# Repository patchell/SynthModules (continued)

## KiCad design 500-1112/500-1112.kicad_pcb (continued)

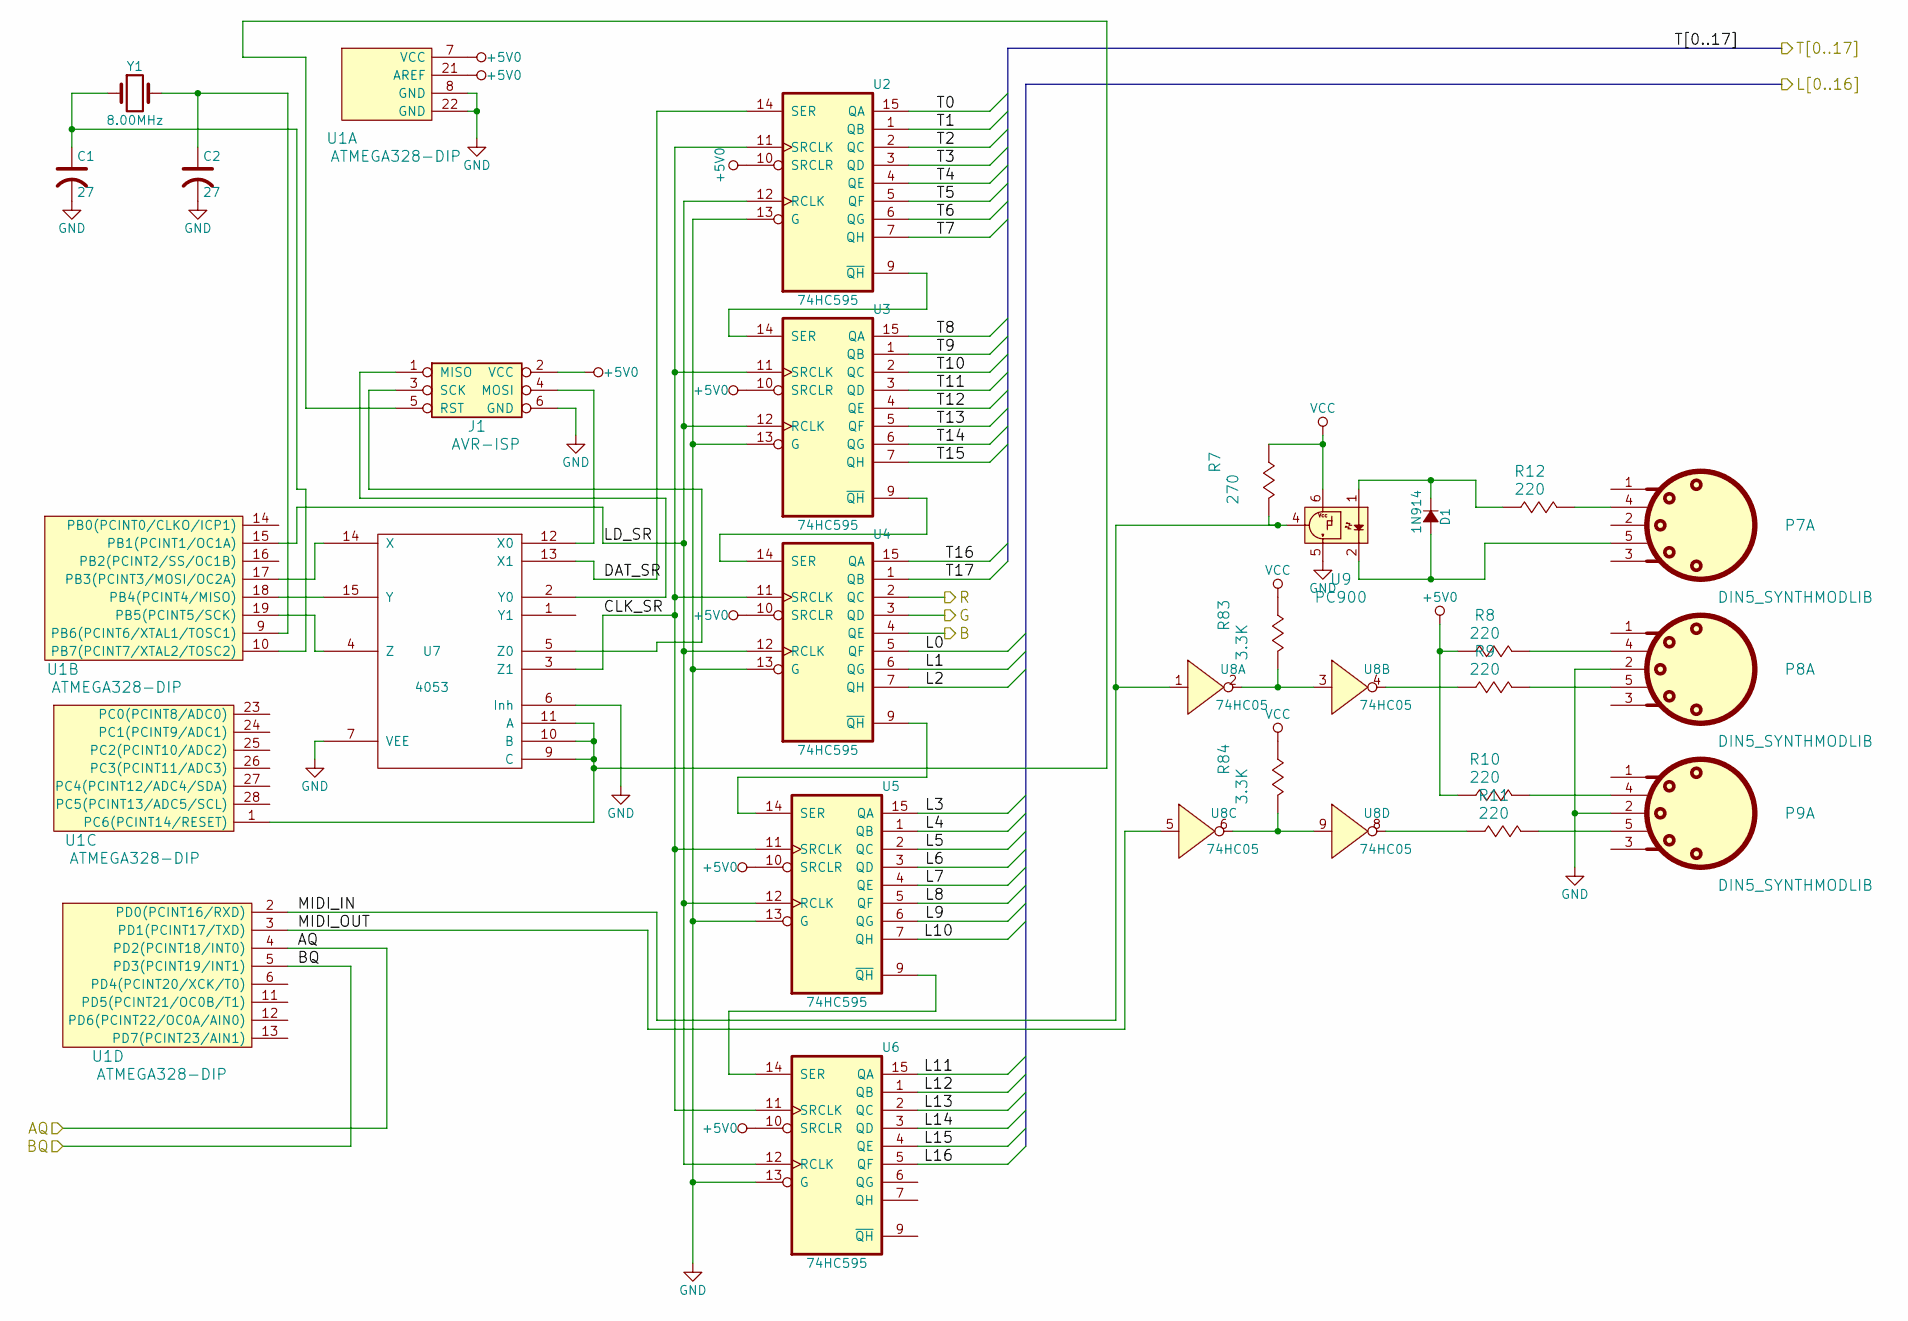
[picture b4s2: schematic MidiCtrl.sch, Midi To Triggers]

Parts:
C1, C2: 27; CAP-0.1
D1: 1N914; DIODE0.4
J1: AVR-ISP; IDC3X2
P7, P8, P9: DIN5_SYNTHMODLIB; DIN-5-PIN
R7: 270; AXIAL0.4
R8, R9, R10, R11, R12: 220; AXIAL0.4
R83, R84: 3.3K; AXIAL0.4
U1: ATMEGA328-DIP; DIP28.3
U2, U3, U4, U5, U6: 74HC595; DIP-20.3
U7: 4053; DIP16.3
U8: 74HC05; DIP-14.3
U9: PC900; DIP-6.3
Y1: 8.00MHz; XTAL

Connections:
+5V0: J1.2 (VCC), R8.1 (A), R10.1 (A), U1.7 (VCC), U1.21 (AREF), U2.10 (SRCLR), U3.10 (SRCLR), U4.10 (SRCLR), U5.10 (SRCLR), U6.10 (SRCLR); also elsewhere on the board
/Midi Controller/AQ: U1.4 (PD2(PCINT18/INT0)); also elsewhere on the board
/Midi Controller/B: U4.4 (QE); also elsewhere on the board
/Midi Controller/BQ: U1.5 (PD3(PCINT19/INT1)); also elsewhere on the board
/Midi Controller/CLK_SR: U2.11 (SRCLK), U3.11 (SRCLK), U4.11 (SRCLK), U5.11 (SRCLK), U6.11 (SRCLK), U7.3 (Z1)
/Midi Controller/DAT_SR: U2.14 (SER), U7.13 (X1)
/Midi Controller/G: U4.3 (QD); also elsewhere on the board
/Midi Controller/L0: U4.5 (QF); also elsewhere on the board
/Midi Controller/L1: U4.6 (QG); also elsewhere on the board
/Midi Controller/L2: U4.7 (QH); also elsewhere on the board
/Midi Controller/L3: U5.15 (QA); also elsewhere on the board
/Midi Controller/L4: U5.1 (QB); also elsewhere on the board
/Midi Controller/L5: U5.2 (QC); also elsewhere on the board
/Midi Controller/L6: U5.3 (QD); also elsewhere on the board
/Midi Controller/L7: U5.4 (QE); also elsewhere on the board
/Midi Controller/L8: U5.5 (QF); also elsewhere on the board
/Midi Controller/L9: U5.6 (QG); also elsewhere on the board
/Midi Controller/L10: U5.7 (QH); also elsewhere on the board
/Midi Controller/L11: U6.15 (QA); also elsewhere on the board
/Midi Controller/L12: U6.1 (QB); also elsewhere on the board
/Midi Controller/L13: U6.2 (QC); also elsewhere on the board
/Midi Controller/L14: U6.3 (QD); also elsewhere on the board
/Midi Controller/L15: U6.4 (QE); also elsewhere on the board
/Midi Controller/L16: U6.5 (QF); also elsewhere on the board
/Midi Controller/LD_SR: U1.15 (PB1(PCINT1/OC1A)), U2.12 (RCLK), U3.12 (RCLK), U4.12 (RCLK), U5.12 (RCLK), U6.12 (RCLK)
/Midi Controller/MIDI_IN: R7.2 (B), U1.2 (PD0(PCINT16/RXD)), U8.1, U9.4 (OUT)
/Midi Controller/MIDI_OUT: U1.3 (PD1(PCINT17/TXD)), U8.5
/Midi Controller/R: U4.2 (QC); also elsewhere on the board
/T0: U2.15 (QA); also elsewhere on the board
/T1: U2.1 (QB); also elsewhere on the board
/T2: U2.2 (QC); also elsewhere on the board
/T3: U2.3 (QD); also elsewhere on the board
/T4: U2.4 (QE); also elsewhere on the board
/T5: U2.5 (QF); also elsewhere on the board
/T6: U2.6 (QG); also elsewhere on the board
/T7: U2.7 (QH); also elsewhere on the board
/T8: U3.15 (QA); also elsewhere on the board
/T9: U3.1 (QB); also elsewhere on the board
/T10: U3.2 (QC); also elsewhere on the board
/T11: U3.3 (QD); also elsewhere on the board
/T12: U3.4 (QE); also elsewhere on the board
/T13: U3.5 (QF); also elsewhere on the board
/T14: U3.6 (QG); also elsewhere on the board
/T15: U3.7 (QH); also elsewhere on the board
/T16: U4.15 (QA); also elsewhere on the board
/T17: U4.1 (QB); also elsewhere on the board
GND: C1.2, C2.2, J1.6 (GND), P8.2, P9.2, U1.8 (GND), U1.22 (GND), U2.8 (GND), U2.13 (G), U3.8 (GND), U3.13 (G), U4.8 (GND), U4.13 (G), U5.8 (GND), U5.13 (G), U6.8 (GND), U6.13 (G), U7.6 (Inh), U7.7 (VEE), U9.5 (GND); also elsewhere on the board
unnamed: C1.1, U1.10 (PB7(PCINT7/XTAL2/TOSC2)), Y1.1
unnamed: C2.1, U1.9 (PB6(PCINT6/XTAL1/TOSC1)), Y1.2
unnamed: D1.1 (K), R12.1 (A), U9.1 (A)
unnamed: D1.2 (A), P7.5, U9.2 (C)
unnamed: J1.1 (MISO), U7.2 (Y0)
unnamed: J1.3 (SCK), U7.5 (Z0)
unnamed: J1.4 (MOSI), U7.12 (X0)
unnamed: J1.5 (RST), U1.1 (PC6(PCINT14/RESET)), U7.9 (C), U7.10 (B), U7.11 (A)
unnamed: P7.4, R12.2 (B)
unnamed: P8.4, R8.2 (B)
unnamed: P8.5, R9.2 (B)
unnamed: P9.4, R10.2 (B)
unnamed: P9.5, R11.2 (B)
unnamed: R9.1 (A), U8.4
unnamed: R11.1 (A), U8.8
unnamed: R83.2 (B), U8.2, U8.3
unnamed: R84.2 (B), U8.6, U8.9
unnamed: U1.17 (PB3(PCINT3/MOSI/OC2A)), U7.14 (X)
unnamed: U1.18 (PB4(PCINT4/MISO)), U7.15 (Y)
unnamed: U1.19 (PB5(PCINT5/SCK)), U7.4 (Z)
unnamed: U2.9 (~QH), U3.14 (SER)
unnamed: U3.9 (~QH), U4.14 (SER)
unnamed: U4.9 (~QH), U5.14 (SER)
unnamed: U5.9 (~QH), U6.14 (SER)
VCC: R7.1 (A), R83.1 (A), R84.1 (A), U2.16 (VCC), U3.16 (VCC), U4.16 (VCC), U5.16 (VCC), U6.16 (VCC), U9.6 (VCC)

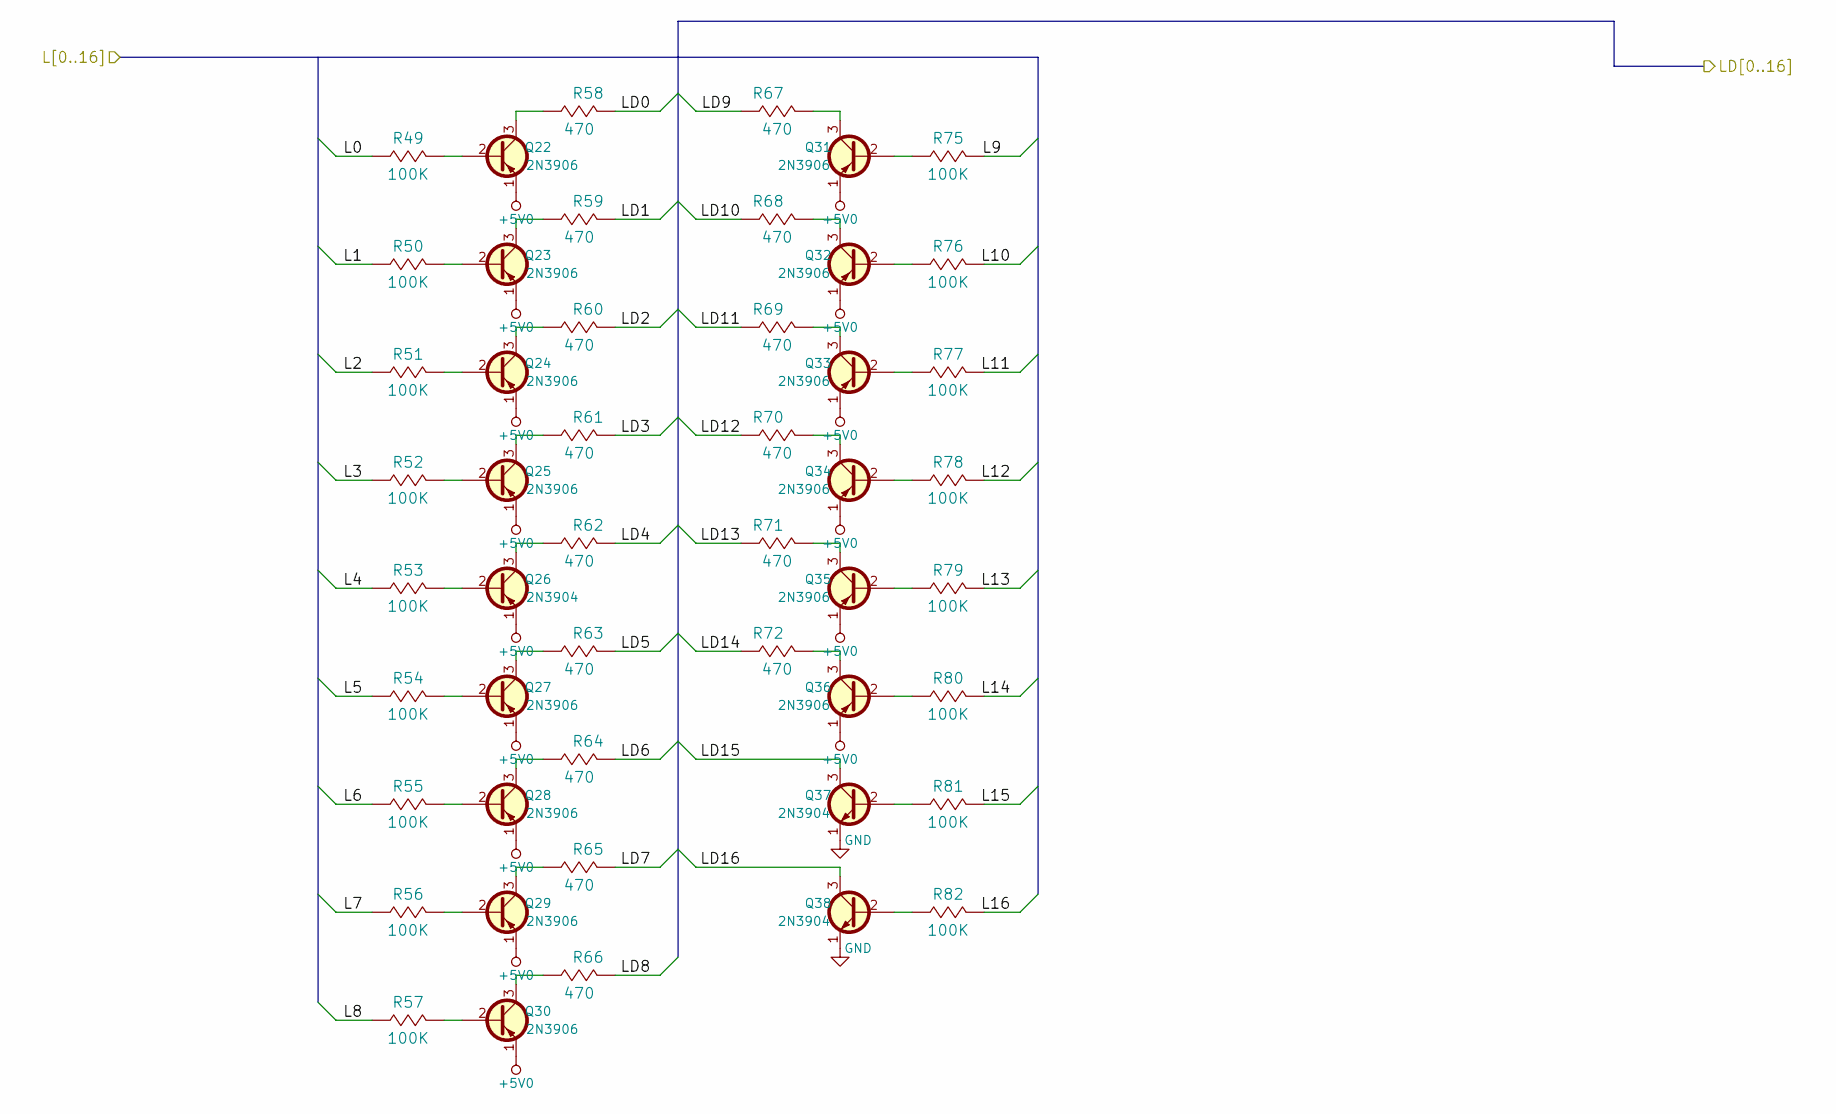
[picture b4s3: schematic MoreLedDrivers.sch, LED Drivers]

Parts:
Q22, Q23, Q24, Q25, Q27, Q28, Q29, Q30, Q31, Q32, Q33, Q34, Q35, Q36: 2N3906; TO92
Q26, Q37, Q38: 2N3904; TO92
R49, R50, R51, R52, R53, R54, R55, R56, R57, R75, R76, R77, R78, R79, R80, R81, R82: 100K; AXIAL0.4
R58, R59, R60, R61, R62, R63, R64, R65, R66, R67, R68, R69, R70, R71, R72: 470; AXIAL0.4

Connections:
+5V0: Q22.1 (E), Q23.1 (E), Q24.1 (E), Q25.1 (E), Q26.1 (E), Q27.1 (E), Q28.1 (E), Q29.1 (E), Q30.1 (E), Q31.1 (E), Q32.1 (E), Q33.1 (E), Q34.1 (E), Q35.1 (E), Q36.1 (E); also elsewhere on the board
/LD0: R58.2 (B); also elsewhere on the board
/LD1: R59.2 (B); also elsewhere on the board
/LD2: R60.2 (B); also elsewhere on the board
/LD3: R61.2 (B); also elsewhere on the board
/LD4: R62.2 (B); also elsewhere on the board
/LD5: R63.2 (B); also elsewhere on the board
/LD6: R64.2 (B); also elsewhere on the board
/LD7: R65.2 (B); also elsewhere on the board
/LD8: R66.2 (B); also elsewhere on the board
/LD9: R67.2 (B); also elsewhere on the board
/LD10: R68.2 (B); also elsewhere on the board
/LD11: R69.2 (B); also elsewhere on the board
/LD12: R70.2 (B); also elsewhere on the board
/LD13: R71.2 (B); also elsewhere on the board
/LD14: R72.2 (B); also elsewhere on the board
/LD15: Q37.3 (C); also elsewhere on the board
/LD16: Q38.3 (C); also elsewhere on the board
/Midi Controller/L0: R49.1 (A); also elsewhere on the board
/Midi Controller/L1: R50.1 (A); also elsewhere on the board
/Midi Controller/L2: R51.1 (A); also elsewhere on the board
/Midi Controller/L3: R52.1 (A); also elsewhere on the board
/Midi Controller/L4: R53.1 (A); also elsewhere on the board
/Midi Controller/L5: R54.1 (A); also elsewhere on the board
/Midi Controller/L6: R55.1 (A); also elsewhere on the board
/Midi Controller/L7: R56.1 (A); also elsewhere on the board
/Midi Controller/L8: R57.1 (A); also elsewhere on the board
/Midi Controller/L9: R75.1 (A); also elsewhere on the board
/Midi Controller/L10: R76.1 (A); also elsewhere on the board
/Midi Controller/L11: R77.1 (A); also elsewhere on the board
/Midi Controller/L12: R78.1 (A); also elsewhere on the board
/Midi Controller/L13: R79.1 (A); also elsewhere on the board
/Midi Controller/L14: R80.1 (A); also elsewhere on the board
/Midi Controller/L15: R81.1 (A); also elsewhere on the board
/Midi Controller/L16: R82.1 (A); also elsewhere on the board
GND: Q37.1 (E), Q38.1 (E); also elsewhere on the board
unnamed: Q22.2 (B), R49.2 (B)
unnamed: Q22.3 (C), R58.1 (A)
unnamed: Q23.2 (B), R50.2 (B)
unnamed: Q23.3 (C), R59.1 (A)
unnamed: Q24.2 (B), R51.2 (B)
unnamed: Q24.3 (C), R60.1 (A)
unnamed: Q25.2 (B), R52.2 (B)
unnamed: Q25.3 (C), R61.1 (A)
unnamed: Q26.2 (B), R53.2 (B)
unnamed: Q26.3 (C), R62.1 (A)
unnamed: Q27.2 (B), R54.2 (B)
unnamed: Q27.3 (C), R63.1 (A)
unnamed: Q28.2 (B), R55.2 (B)
unnamed: Q28.3 (C), R64.1 (A)
unnamed: Q29.2 (B), R56.2 (B)
unnamed: Q29.3 (C), R65.1 (A)
unnamed: Q30.2 (B), R57.2 (B)
unnamed: Q30.3 (C), R66.1 (A)
unnamed: Q31.2 (B), R75.2 (B)
unnamed: Q31.3 (C), R67.1 (A)
unnamed: Q32.2 (B), R76.2 (B)
unnamed: Q32.3 (C), R68.1 (A)
unnamed: Q33.2 (B), R77.2 (B)
unnamed: Q33.3 (C), R69.1 (A)
unnamed: Q34.2 (B), R78.2 (B)
unnamed: Q34.3 (C), R70.1 (A)
unnamed: Q35.2 (B), R79.2 (B)
unnamed: Q35.3 (C), R71.1 (A)
unnamed: Q36.2 (B), R80.2 (B)
unnamed: Q36.3 (C), R72.1 (A)
unnamed: Q37.2 (B), R81.2 (B)
unnamed: Q38.2 (B), R82.2 (B)

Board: 2 copper layers, 143 parts (0 on the bottom side), 188 nets, no tracks yet.

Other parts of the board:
P1, P2, P3: 500-1114; IDC10x2-Vert
P4: 500-1113-AQBKNOB; IDC10x2_Vert
P5: 500-1113-AQB; IDC5x2_Vert
P6: EurorackPower16pin; IDC8x2_Vert
Q1, Q2, Q3: 2N3904; TO92
R1, R2, R3: 100K; AXIAL0.4
R4, R5, R6: 470; AXIAL0.4

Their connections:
+5V0: P1.3, P1.7, P1.11, P1.15, P1.18, P1.19, P2.3, P2.7, P2.11, P2.15, P2.18, P2.19, P3.3, P3.7, P3.11, P3.15, P3.18, P3.19, P5.5, P5.7, P5.9, P6.11, P6.12; also elsewhere on the board
/LD0: P4.1; also elsewhere on the board
/LD1: P4.2; also elsewhere on the board
/LD2: P4.3; also elsewhere on the board
/LD3: P4.4; also elsewhere on the board
/LD4: P4.5; also elsewhere on the board
/LD5: P4.6; also elsewhere on the board
/LD6: P4.7; also elsewhere on the board
/LD7: P4.8; also elsewhere on the board
/LD8: P4.9; also elsewhere on the board
/LD9: P4.10; also elsewhere on the board
/LD10: P4.11; also elsewhere on the board
/LD11: P4.12; also elsewhere on the board
/LD12: P4.13; also elsewhere on the board
/LD13: P4.14; also elsewhere on the board
/LD14: P4.15; also elsewhere on the board
/LD15: P4.17; also elsewhere on the board
/LD16: P4.18; also elsewhere on the board
/Midi Controller/AQ: P5.2; also elsewhere on the board
/Midi Controller/B: R2.1; also elsewhere on the board
/Midi Controller/BQ: P5.4; also elsewhere on the board
/Midi Controller/G: R3.1; also elsewhere on the board
/Midi Controller/R: R1.1; also elsewhere on the board
/T0: P1.1; also elsewhere on the board
/T1: P1.5; also elsewhere on the board
/T2: P1.9; also elsewhere on the board
/T3: P1.13; also elsewhere on the board
/T4: P1.17; also elsewhere on the board
/T5: P1.20; also elsewhere on the board
/T6: P2.1; also elsewhere on the board
/T7: P2.5; also elsewhere on the board
/T8: P2.9; also elsewhere on the board
/T9: P2.13; also elsewhere on the board
/T10: P2.17; also elsewhere on the board
/T11: P2.20; also elsewhere on the board
/T12: P3.1; also elsewhere on the board
/T13: P3.5; also elsewhere on the board
/T14: P3.9; also elsewhere on the board
/T15: P3.13; also elsewhere on the board
/T16: P3.17; also elsewhere on the board
/T17: P3.20; also elsewhere on the board
/TLD0: P1.2; also elsewhere on the board
/TLD1: P1.4; also elsewhere on the board
/TLD2: P1.6; also elsewhere on the board
/TLD3: P1.8; also elsewhere on the board
/TLD4: P1.10; also elsewhere on the board
/TLD5: P1.16; also elsewhere on the board
/TLD6: P2.2; also elsewhere on the board
/TLD7: P2.4; also elsewhere on the board
/TLD8: P2.6; also elsewhere on the board
/TLD9: P2.8; also elsewhere on the board
/TLD10: P2.10; also elsewhere on the board
/TLD11: P2.16; also elsewhere on the board
/TLD12: P3.2; also elsewhere on the board
/TLD13: P3.4; also elsewhere on the board
/TLD14: P3.6; also elsewhere on the board
/TLD15: P3.8; also elsewhere on the board
/TLD16: P3.10; also elsewhere on the board
/TLD17: P3.16; also elsewhere on the board
GND: P5.1, P5.3, P6.3, P6.4, P6.5, P6.6, P6.7, P6.8, Q1.1, Q2.1, Q3.1; also elsewhere on the board
unnamed: P5.6, R4.2
unnamed: P5.8, R6.2
unnamed: P5.10, R5.2
unnamed: P6.1, P6.2
unnamed: P6.9, P6.10
unnamed: P6.13, P6.14
unnamed: P6.15, P6.16
unnamed: Q1.2, R1.2
unnamed: Q1.3, R4.1
unnamed: Q2.2, R2.2
unnamed: Q2.3, R5.1
unnamed: Q3.2, R3.2
unnamed: Q3.3, R6.1

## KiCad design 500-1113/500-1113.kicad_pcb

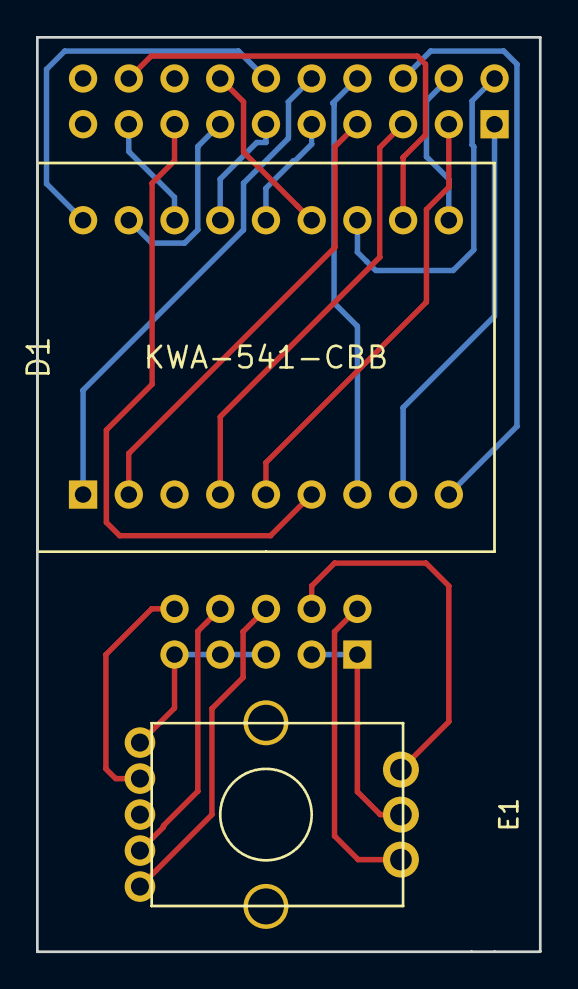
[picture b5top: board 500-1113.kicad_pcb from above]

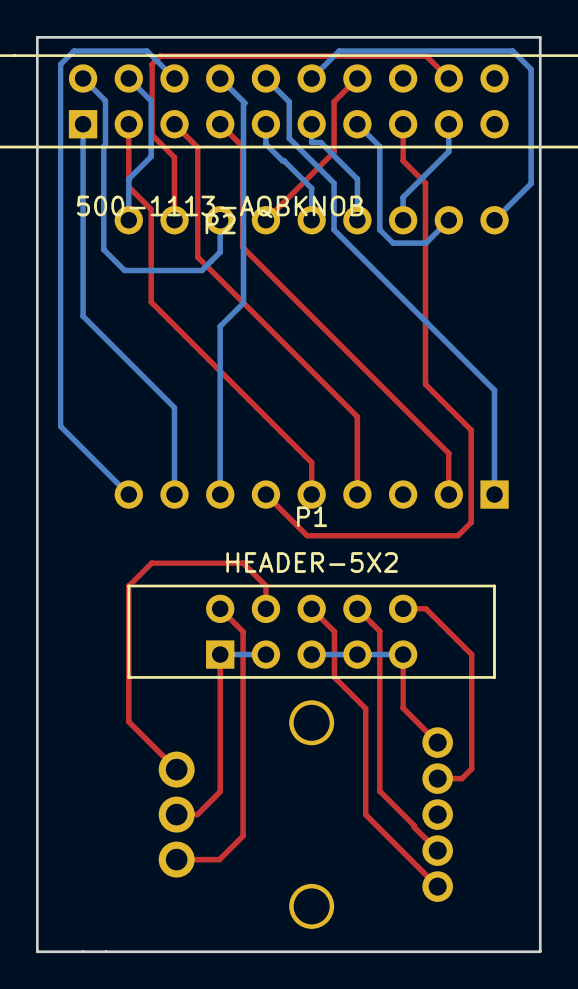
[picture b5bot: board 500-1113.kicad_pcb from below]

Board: 2 copper layers, 27.9 x 50.8 mm, 4 parts (2 on the bottom side), 24 nets.

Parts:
D1: KWA-541-CBB; LED-DISPLAY-DUAL-DIGIT
E1: ROTARY-ENCODER-RGB-SPARKFUN; Rotary-Encoder-RGB-Sparkfun
P1: HEADER-5X2; IDC5x2_Vert
P2: 500-1113-AQBKNOB; IDC10x2-Vert

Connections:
unnamed: D1.1, P2.10
unnamed: D1.2, P2.7
unnamed: D1.4, P2.5
unnamed: D1.5, P2.3
unnamed: D1.6, P2.15
unnamed: D1.7, P2.8
unnamed: D1.8, P2.1
unnamed: D1.9, P2.6
unnamed: D1.10, P2.4
unnamed: D1.11, P2.18
unnamed: D1.12, P2.2
unnamed: D1.13, P2.14
unnamed: D1.14, P2.9
unnamed: D1.15, P2.11
unnamed: D1.16, P2.17
unnamed: D1.17, P2.13
unnamed: D1.18, P2.12
unnamed: E1.1, P1.6
unnamed: E1.2, P1.8
unnamed: E1.4, P1.10
unnamed: E1.5, P1.5, P1.7, P1.9
unnamed: E1.6, P1.2
unnamed: E1.7, P1.1, P1.3
unnamed: E1.8, P1.4

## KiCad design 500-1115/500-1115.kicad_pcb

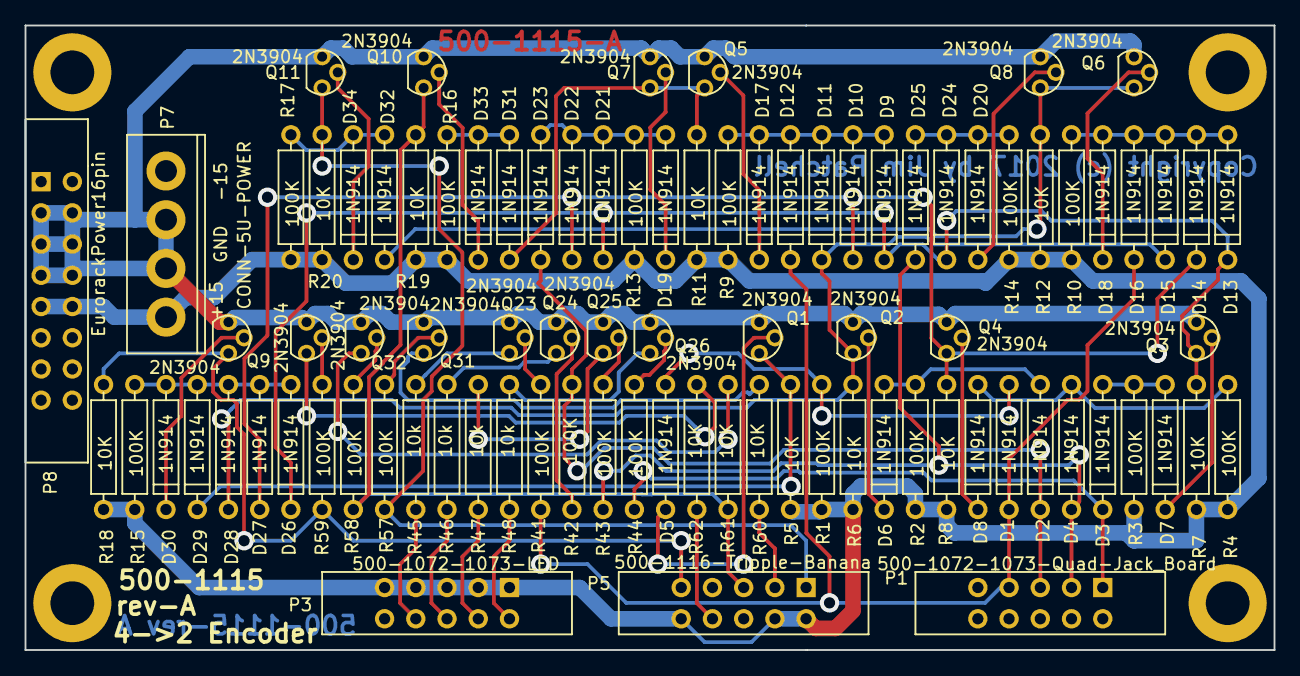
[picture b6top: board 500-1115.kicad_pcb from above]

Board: 2 copper layers, 101.6 x 50.8 mm, 95 parts (0 on the bottom side), 57 nets.

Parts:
D1, D2, D3, D4, D5, D6, D7, D8, D9, D10, D11, D12, D13, D14, D15, D16, D17, D18, D19, D20, D21, D22, D23, D24, D25, D26, D27, D28, D29, D30, D31, D32, D33, D34: 1N914; DIODE0.4
P1: 500-1072-1073-Quad-Jack_Board; IDC5x2_Vert
P3: 500-1072-1073-LED; IDC5x2_Vert
P5: 500-1116-Tripple-Banana; IDC5x2_Vert
P7: CONN-5U-POWER; CONN-5U-POWER-VERT
P8: EurorackPower16pin; IDC8x2_Vert
PAD1, PAD2, PAD3, PAD4: PAD; MountingHole_140
Q1, Q2, Q3, Q4, Q5, Q6, Q7, Q8, Q9, Q10, Q11, Q23, Q24, Q25, Q26, Q31, Q32, Q33: 2N3904; TO92
R1, R2, R3, R4, R9, R10, R13, R14, R15, R16, R17, R41, R42, R43, R44, R57, R58, R59: 100K; AXIAL0.4
R5, R6, R7, R8, R11, R12, R18, R19, R20, R60, R61, R62: 10K; AXIAL0.4
R45, R46, R47, R48: 10k; AXIAL0.4

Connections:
+15V0: P3.1, P3.3, P3.5, P3.7, P3.9, P5.2, P5.4, P5.10, P7.1, P8.9, P8.10, R1.1, R2.1, R3.1, R4.1, R5.1, R6.1, R7.1, R8.1, R9.1, R10.1, R11.1, R12.1, R13.1, R14.1, R15.1, R16.1, R17.1, R18.1, R19.1, R20.1
/Driver3_1/I0: P5.1, Q11.3, R20.2, R57.1
/Driver3_1/I1: P5.5, Q10.3, R19.2, R58.1, R61.2
/Driver3_1/O0: P5.3, R60.2
/Driver3_1/O2: P5.8, R62.2
/LedDrv4_1/OUT1: P3.2, R48.2
/LedDrv4_1/OUT2: P3.4, R47.2
/LedDrv4_1/OUT3: P3.6, R46.2
/LedDrv4_1/OUT4: P3.8, R45.2
/Logic_1/A: D3.1, P1.1, R44.1
/Logic_1/B: D4.1, D25.1, P1.3, R43.1
/Logic_1/C: D2.1, D23.1, P1.5, R42.1
/Logic_1/D: D1.1, D12.1, D16.1, P1.7, R41.1
/Logic_1/E: P5.9, Q9.3, R18.2, R59.1
GND: P7.2, P7.3, P8.3, P8.4, P8.5, P8.6, P8.7, P8.8, Q1.1, Q2.1, Q3.1, Q4.1, Q5.1, Q6.1, Q7.1, Q8.1, Q9.1, Q10.1, Q11.1, Q23.1, Q24.1, Q25.1, Q26.1, Q31.1, Q32.1, Q33.1
unnamed: D1.2, D5.2, R1.2
unnamed: D2.2, D6.2, R2.2
unnamed: D3.2, D7.2, R3.2
unnamed: D4.2, D8.2, R4.2
unnamed: D5.1, Q1.2
unnamed: D6.1, Q2.2
unnamed: D7.1, Q3.2
unnamed: D8.1, Q4.2
unnamed: D10.1, D14.1, D22.1, D27.1, Q4.3, R8.2
unnamed: D9.2, D10.2, D11.2, D12.2, D17.2, R9.2
unnamed: D11.1, D15.1, D28.1, Q2.3, R6.2
unnamed: D9.1, D13.1, D21.1, D24.1, D26.1, Q3.3, R7.2
unnamed: D13.2, D14.2, D15.2, D16.2, D18.2, R10.2
unnamed: D17.1, Q5.2
unnamed: D18.1, Q6.2
unnamed: D19.1, Q7.2
unnamed: D19.2, D21.2, D22.2, D23.2, R13.2
unnamed: D20.1, Q8.2
unnamed: D20.2, D24.2, D25.2, R14.2
unnamed: D26.2, D27.2, D28.2, D29.2, D30.2, R15.2
unnamed: D29.1, Q1.3, R5.2
unnamed: D30.1, Q9.2
unnamed: D31.1, Q5.3, Q7.3, R11.2
unnamed: D31.2, D33.2, R16.2
unnamed: D32.1, Q6.3, Q8.3, R12.2
unnamed: D32.2, D34.2, R17.2
unnamed: D33.1, Q10.2
unnamed: D34.1, Q11.2
unnamed: Q23.2, R41.2
unnamed: Q23.3, R45.1
unnamed: Q24.2, R42.2
unnamed: Q24.3, R46.1
unnamed: Q25.2, R43.2
unnamed: Q25.3, R47.1
unnamed: Q26.2, R44.2
unnamed: Q26.3, R48.1
unnamed: Q31.2, R57.2
unnamed: Q31.3, R60.1
unnamed: Q32.2, R58.2
unnamed: Q32.3, R61.1
unnamed: Q33.2, R59.2
unnamed: Q33.3, R62.1

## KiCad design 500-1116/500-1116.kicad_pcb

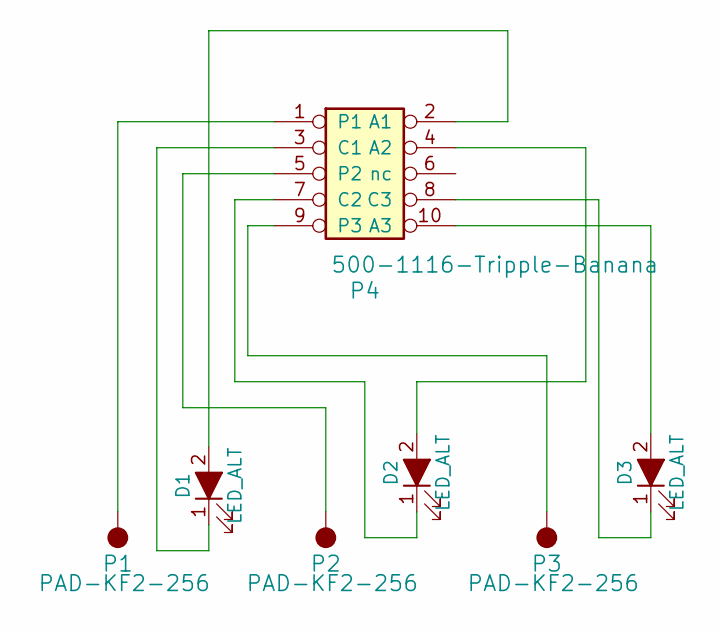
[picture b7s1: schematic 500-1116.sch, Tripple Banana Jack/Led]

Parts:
D1, D2, D3: LED_ALT; LED_D5.0mm
P1, P2, P3: PAD-KF2-256; KF2-256-TerminalPad
P4: 500-1116-Tripple-Banana; IDC5x2_Vert

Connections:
unnamed: D1.1 (K), P4.3 (C1)
unnamed: D1.2 (A), P4.2 (A1)
unnamed: D2.1 (K), P4.7 (C2)
unnamed: D2.2 (A), P4.4 (A2)
unnamed: D3.1 (K), P4.8 (C3)
unnamed: D3.2 (A), P4.10 (A3)
unnamed: P1.1, P4.1
unnamed: P2.1, P4.5 (P2)
unnamed: P3.1, P4.9 (P3)

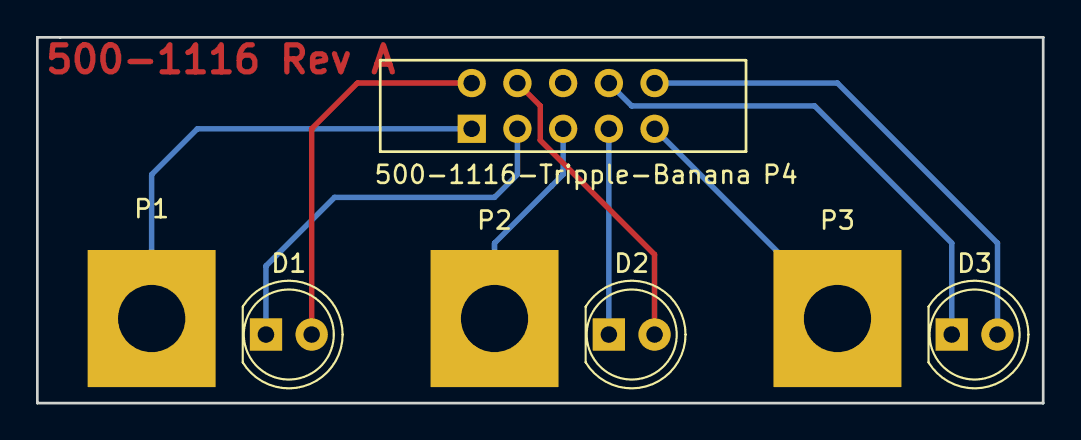
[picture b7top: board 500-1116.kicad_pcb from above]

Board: 2 copper layers, 55.9 x 20.3 mm, 7 parts (0 on the bottom side), 9 nets.

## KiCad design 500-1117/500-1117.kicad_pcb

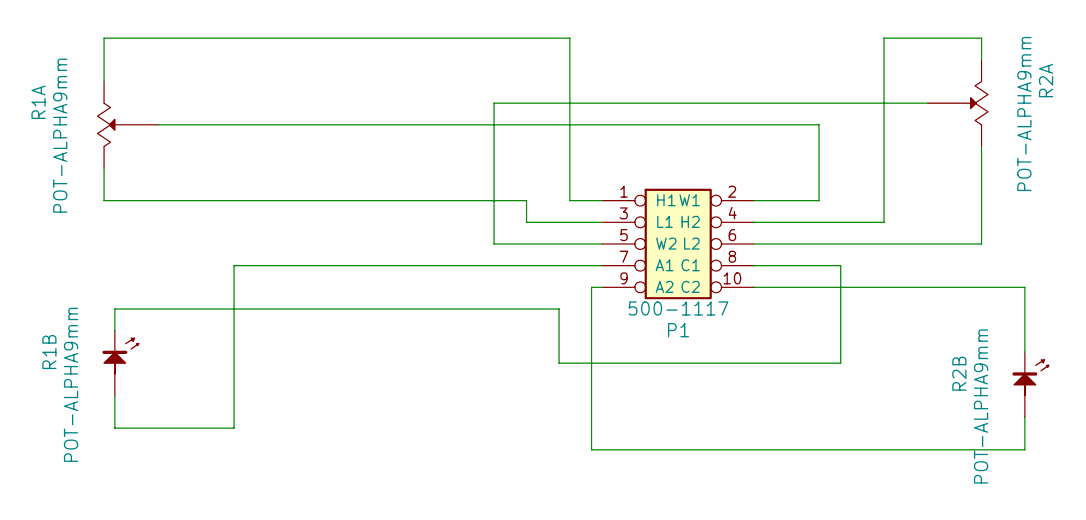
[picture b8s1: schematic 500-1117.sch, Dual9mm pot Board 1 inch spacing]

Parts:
P1: 500-1117; IDC5x2_Vert
R1, R2: POT-ALPHA9mm; Alpha9mmPotWithLED

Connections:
unnamed: P1.1 (H1), R1.1 (A)
unnamed: P1.2 (W1), R1.2 (Wiper)
unnamed: P1.3 (L1), R1.3 (B)
unnamed: P1.4 (H2), R2.1 (A)
unnamed: P1.5 (W2), R2.2 (Wiper)
unnamed: P1.6 (L2), R2.3 (B)
unnamed: P1.7 (A1), R1.5 (ANODE)
unnamed: P1.8 (C1), R1.4 (CATHODE)
unnamed: P1.9 (A2), R2.5 (ANODE)
unnamed: P1.10 (C2), R2.4 (CATHODE)

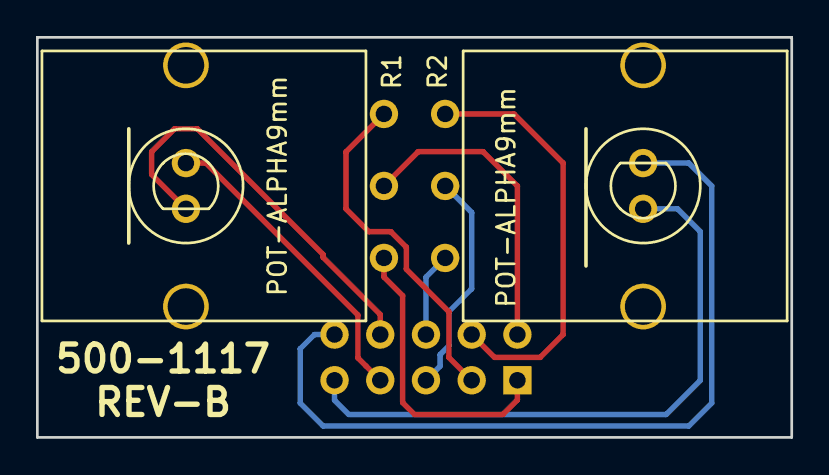
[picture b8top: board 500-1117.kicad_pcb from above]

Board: 2 copper layers, 41.9 x 22.2 mm, 3 parts (1 on the bottom side), 10 nets.
